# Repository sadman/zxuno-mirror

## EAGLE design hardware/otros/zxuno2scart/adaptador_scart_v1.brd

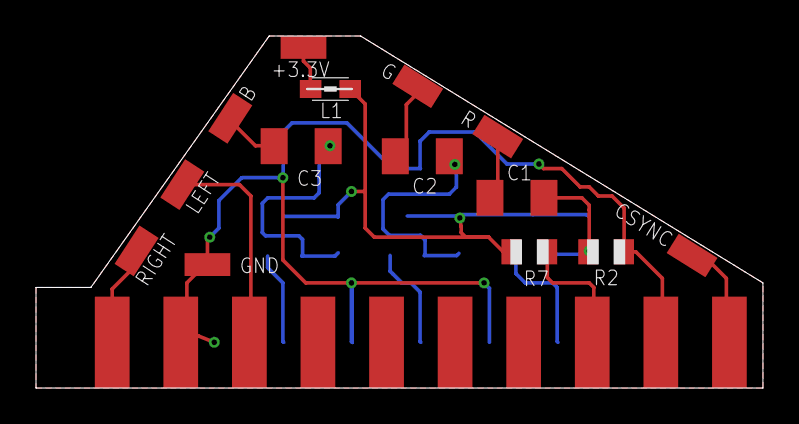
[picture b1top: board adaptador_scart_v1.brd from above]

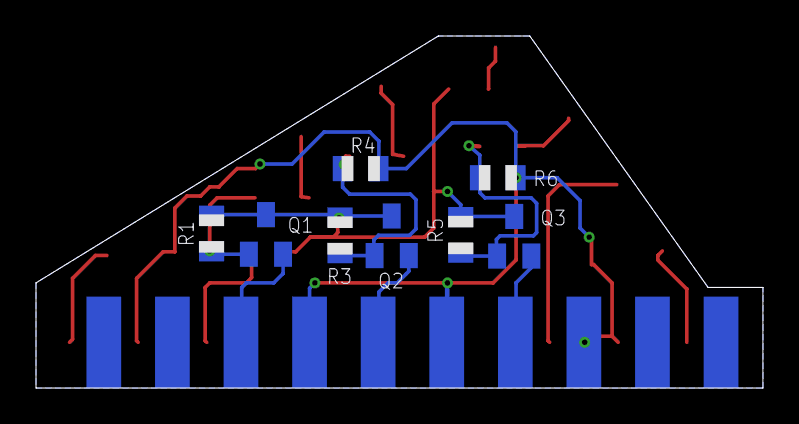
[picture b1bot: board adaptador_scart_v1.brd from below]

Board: 2 copper layers, 40.4 x 19.6 mm, 23 parts (9 on the bottom side), 16 nets.

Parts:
+3.3V: SMD1,27-2,54
B: SMD1,27-2,54
C1, C2, C3: 1uF; C1206K
CSYNC: SMD1,27-2,54
G: SMD1,27-2,54
GND: SMD1,27-2,54
L1: 0805
LEFT: SMD1,27-2,54
Q1, Q2, Q3: BC847C; SOT23
R: SMD1,27-2,54
R1, R3, R5: 10K; R0805
R2, R4, R6: 22K; R0805
R7: 50; R0805
RIGHT: SMD1,27-2,54
U$1: SCART-MALE-PCB; SCART-PCB

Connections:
BIN: B.1, C3.1
BOUT: Q3.2, U$1.7
CSYNC: CSYNC.1, U$1.20
FS: R7.1, U$1.16
GIN: C2.1, G.1
GND: GND.1, R2.1, R4.1, R6.1, U$1.4, U$1.5, U$1.9, U$1.13, U$1.18
GOUT: Q2.2, U$1.11
LEFT: LEFT.1, U$1.6
unnamed: C1.2, Q1.1, R1.1, R2.2
unnamed: C3.2, Q3.1, R5.1, R6.2
unnamed: C2.2, Q2.1, R3.1, R4.2
RIGHT: RIGHT.1, U$1.2
RIN: C1.1, R.1
ROUT: Q1.2, U$1.15
VCC: L1.2, Q1.3, Q2.3, Q3.3, R1.2, R3.2, R5.2, R7.2
VCCIN: +3.3V.1, L1.1

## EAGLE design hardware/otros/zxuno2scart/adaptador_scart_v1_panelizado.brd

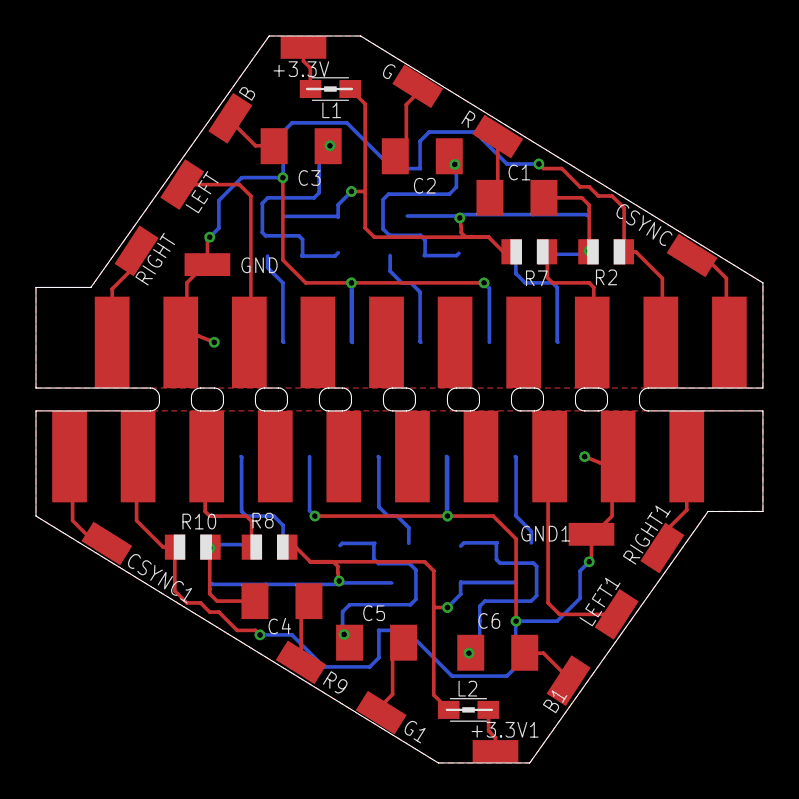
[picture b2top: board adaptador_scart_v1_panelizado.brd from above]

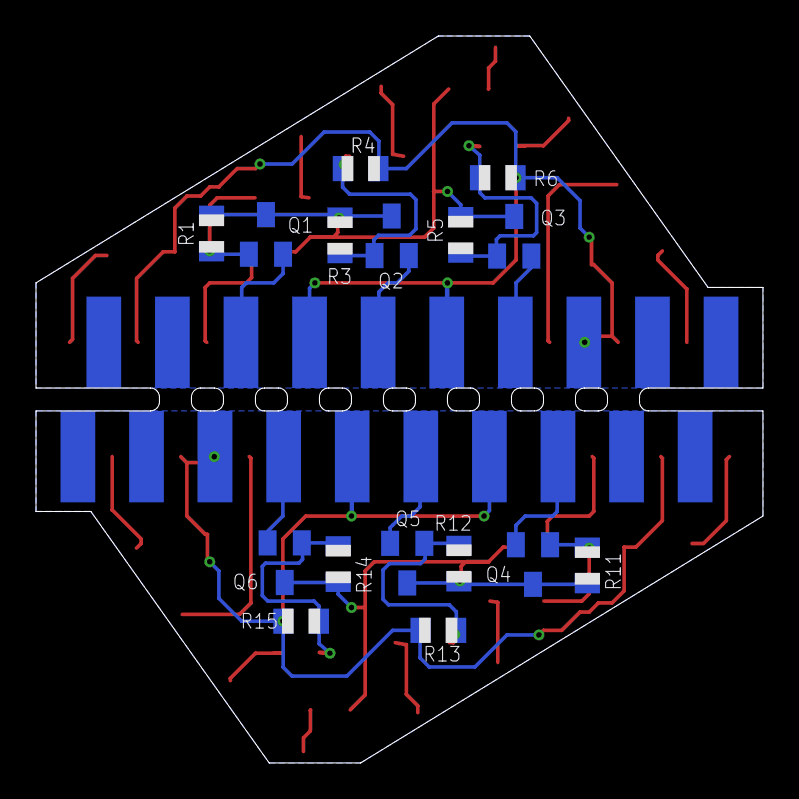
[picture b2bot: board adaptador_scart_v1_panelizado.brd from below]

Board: 2 copper layers, 40.4 x 40.4 mm, 46 parts (18 on the bottom side), 32 nets.

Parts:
+3.3V, +3.3V1: SMD1,27-2,54
B, B1: SMD1,27-2,54
C1, C2, C3, C4, C5, C6: 1uF; C1206K
CSYNC, CSYNC1: SMD1,27-2,54
G, G1: SMD1,27-2,54
GND, GND1: SMD1,27-2,54
L1, L2: 0805
LEFT, LEFT1: SMD1,27-2,54
Q1, Q2, Q3, Q4, Q5, Q6: BC847C; SOT23
R, R9: SMD1,27-2,54
R1, R3, R5, R11, R12, R14: 10K; R0805
R2, R4, R6, R10, R13, R15: 22K; R0805
R7, R8: 50; R0805
RIGHT, RIGHT1: SMD1,27-2,54
U$1, U$2: SCART-MALE-PCB; SCART-PCB

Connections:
BIN: B.1, C3.1
BIN1: B1.1, C6.1
BOUT: Q3.2, U$1.7
BOUT1: Q6.2, U$2.7
CSYNC: CSYNC.1, U$1.20
CSYNC1: CSYNC1.1, U$2.20
FS: R7.1, U$1.16
FS1: R8.1, U$2.16
GIN: C2.1, G.1
GIN1: C5.1, G1.1
GND: GND.1, R2.1, R4.1, R6.1, U$1.4, U$1.5, U$1.9, U$1.13, U$1.18
GND1: GND1.1, R10.1, R13.1, R15.1, U$2.4, U$2.5, U$2.9, U$2.13, U$2.18
GOUT: Q2.2, U$1.11
GOUT1: Q5.2, U$2.11
LEFT: LEFT.1, U$1.6
LEFT1: LEFT1.1, U$2.6
unnamed: C4.2, Q4.1, R10.2, R11.1
unnamed: C6.2, Q6.1, R14.1, R15.2
unnamed: C5.2, Q5.1, R12.1, R13.2
unnamed: C1.2, Q1.1, R1.1, R2.2
unnamed: C3.2, Q3.1, R5.1, R6.2
unnamed: C2.2, Q2.1, R3.1, R4.2
RIGHT: RIGHT.1, U$1.2
RIGHT1: RIGHT1.1, U$2.2
RIN: C1.1, R.1
RIN1: C4.1, R9.1
ROUT: Q1.2, U$1.15
ROUT1: Q4.2, U$2.15
VCC: L1.2, Q1.3, Q2.3, Q3.3, R1.2, R3.2, R5.2, R7.2
VCC1: L2.2, Q4.3, Q5.3, Q6.3, R8.2, R11.2, R12.2, R14.2
VCCIN: +3.3V.1, L1.1
VCCIN1: +3.3V1.1, L2.1

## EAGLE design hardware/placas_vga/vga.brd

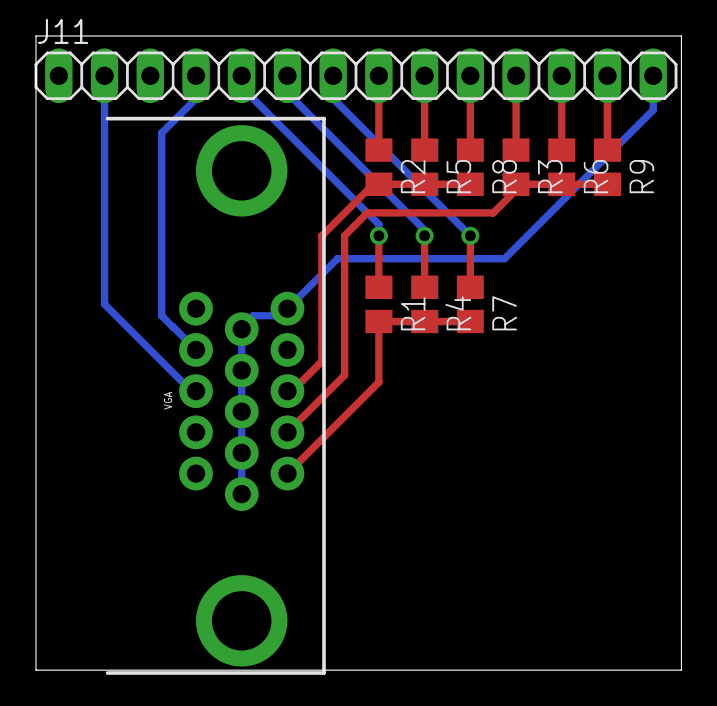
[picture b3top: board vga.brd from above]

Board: 2 copper layers, 35.9 x 35.2 mm, 11 parts (0 on the bottom side), 15 nets.

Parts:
J11: 1X14
R1, R2, R3: 470; R0805
R4, R5, R6: 1K; R0805
R7, R8, R9: 2K; R0805
VGA: DB15

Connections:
BLUE: R3.2, R6.2, R9.2, VGA.2
EXT1: J11.5, R1.1
EXT7: J11.6, R4.1
EXT13: J11.8, R2.1
EXT16: J11.9, R5.1
EXT19: J11.10, R8.1
EXT22: J11.11, R3.1
EXT25: J11.12, R6.1
EXT28: J11.13, R9.1
GREEN: R2.2, R5.2, R8.2, VGA.3
HSYNC: J11.2, VGA.13
unnamed: J11.14, VGA.5, VGA.6, VGA.7, VGA.8, VGA.9, VGA.10
unnamed: J11.7, R7.1
RED: R1.2, R4.2, R7.2, VGA.1
VSYNC: J11.4, VGA.14

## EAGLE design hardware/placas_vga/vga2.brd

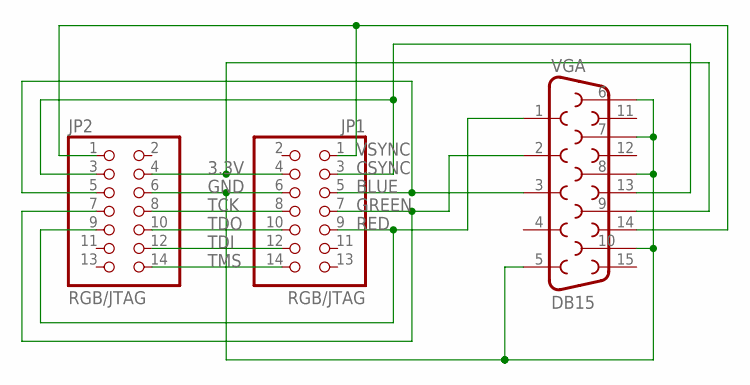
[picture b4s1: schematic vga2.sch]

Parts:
JP1, JP2: RGB/JTAG; 2X07
VGA: DB15

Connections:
3.3V: JP1.4, JP2.4, VGA.9
BLUE: JP1.5, JP2.5, VGA.3
CSYNC: JP1.3, JP2.3, VGA.13
GND: JP1.6, JP2.6, VGA.5, VGA.6, VGA.7, VGA.8, VGA.10
GREEN: JP1.7, JP2.7, VGA.2
RED: JP1.9, JP2.9, VGA.1
TCK: JP1.8, JP2.8
TDI: JP1.12, JP2.12
TDO: JP1.10, JP2.10
TMS: JP1.14, JP2.14
VSYNC: JP1.1, JP2.1, VGA.14

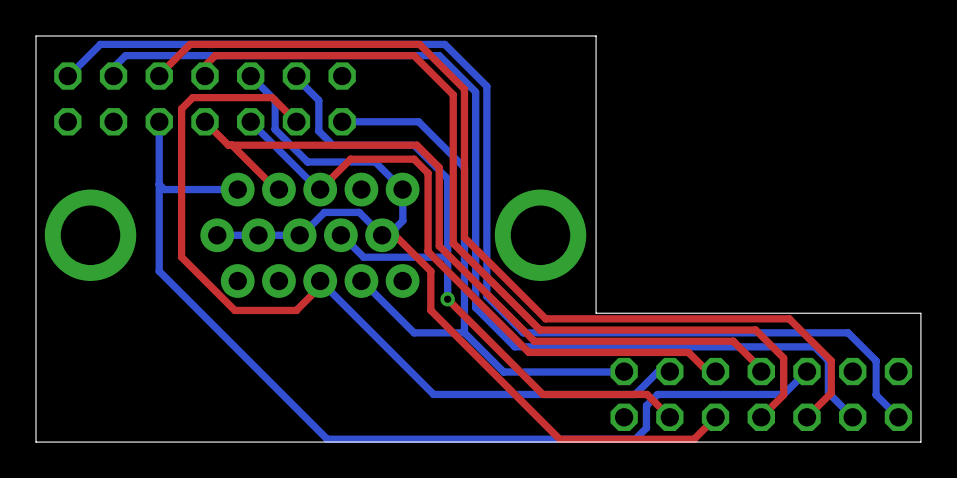
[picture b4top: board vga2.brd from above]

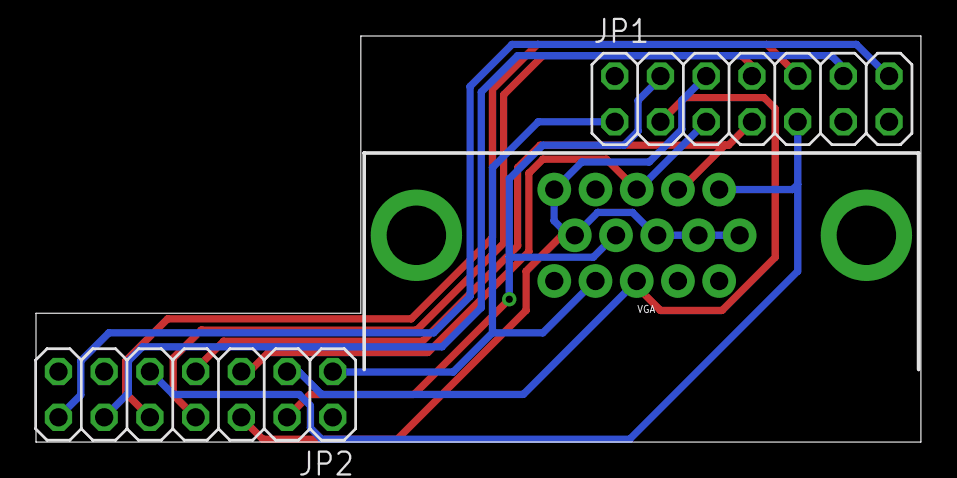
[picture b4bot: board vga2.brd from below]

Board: 2 copper layers, 49.2 x 22.6 mm, 3 parts (3 on the bottom side), 11 nets.

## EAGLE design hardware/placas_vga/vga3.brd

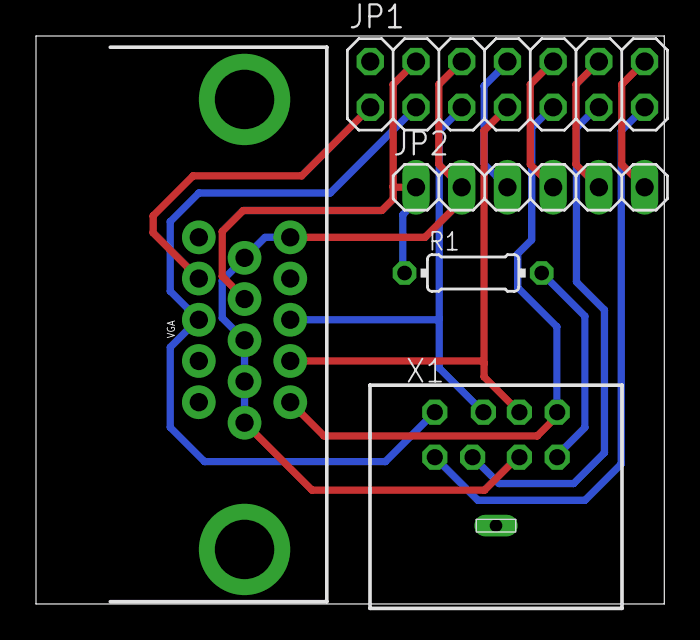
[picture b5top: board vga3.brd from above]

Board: 2 copper layers, 34.9 x 31.6 mm, 5 parts (0 on the bottom side), 14 nets.

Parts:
JP1: RGB/JTAG; 2X07
JP2: JTAG; 1X06
R1: 100; 0204/7
VGA: DB15
X1: MDIN08S

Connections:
3.3V: JP1.4, JP2.1, R1.1, VGA.9
BLUE: JP1.5, VGA.3, X1.7
CSYNC: JP1.3, VGA.13, X1.8
GND: JP1.6, JP2.2, VGA.5, VGA.6, VGA.7, VGA.8, VGA.10, X1.1
GREEN: JP1.7, VGA.2, X1.4
L-OUT: JP1.13, X1.5
unnamed: R1.2, X1.3
R-OUT: JP1.11, X1.2
RED: JP1.9, VGA.1, X1.6
TCK: JP1.8, JP2.3
TDI: JP1.12, JP2.5
TDO: JP1.10, JP2.4
TMS: JP1.14, JP2.6
VSYNC: JP1.1, VGA.14

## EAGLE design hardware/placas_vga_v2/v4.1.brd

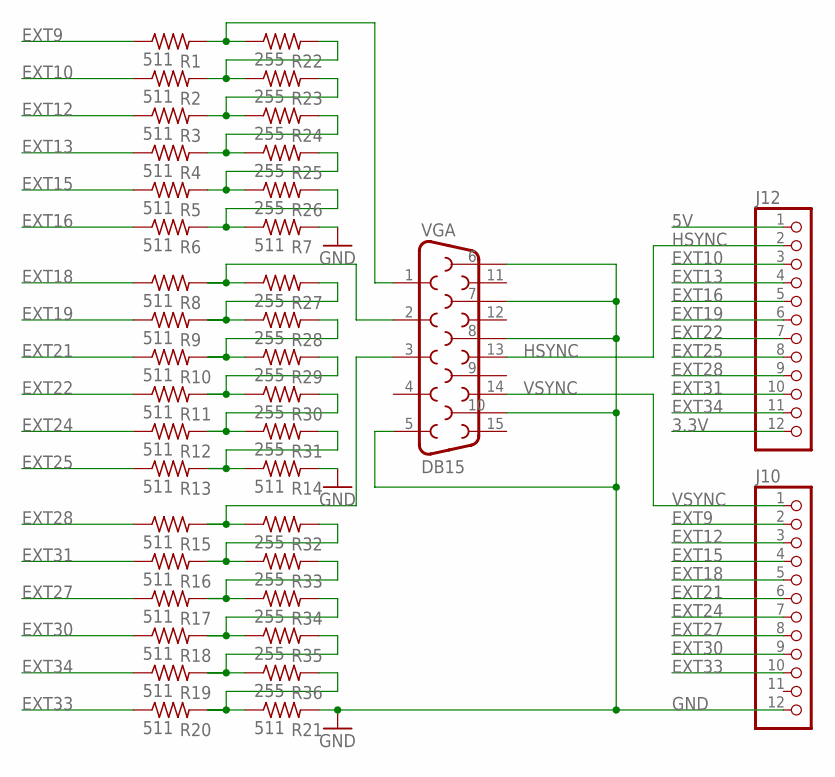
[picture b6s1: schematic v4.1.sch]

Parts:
J10, J12: PINHD-1X12; 1X12
R1, R2, R3, R4, R5, R6, R7, R8, R9, R10, R11, R12, R13, R14, R15, R16, R17, R18, R19, R20, R21: 511; R0805
R22, R23, R24, R25, R26, R27, R28, R29, R30, R31, R32, R33, R34, R35, R36: 255; R0805
VGA: DB15

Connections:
3.3V: J12.12
5V: J12.1
EXT9: J10.2, R1.1
EXT10: J12.3, R2.1
EXT12: J10.3, R3.1
EXT13: J12.4, R4.1
EXT15: J10.4, R5.1
EXT16: J12.5, R6.1
EXT18: J10.5, R8.1
EXT19: J12.6, R9.1
EXT21: J10.6, R10.1
EXT22: J12.7, R11.1
EXT24: J10.7, R12.1
EXT25: J12.8, R13.1
EXT27: J10.8, R17.1
EXT28: J12.9, R15.1
EXT30: J10.9, R18.1
EXT31: J12.10, R16.1
EXT33: J10.10, R20.1
EXT34: J12.11, R19.1
GND: J10.12, R7.2, R14.2, R21.2, VGA.5, VGA.6, VGA.7, VGA.8, VGA.10
GREEN: R8.2, R27.1, VGA.2
HSYNC: J12.2, VGA.13
unnamed: R20.2, R21.1, R36.2
unnamed: R9.2, R27.2, R28.1
unnamed: R2.2, R22.2, R23.1
unnamed: R1.2, R22.1, VGA.1
unnamed: R12.2, R30.2, R31.1
unnamed: R6.2, R7.1, R26.2
unnamed: R3.2, R23.2, R24.1
unnamed: R4.2, R24.2, R25.1
unnamed: R5.2, R25.2, R26.1
unnamed: R11.2, R29.2, R30.1
unnamed: R13.2, R14.1, R31.2
unnamed: R10.2, R28.2, R29.1
unnamed: R15.2, R32.1, VGA.3
unnamed: R16.2, R32.2, R33.1
unnamed: R17.2, R33.2, R34.1
unnamed: R18.2, R34.2, R35.1
unnamed: R19.2, R35.2, R36.1
VSYNC: J10.1, VGA.14

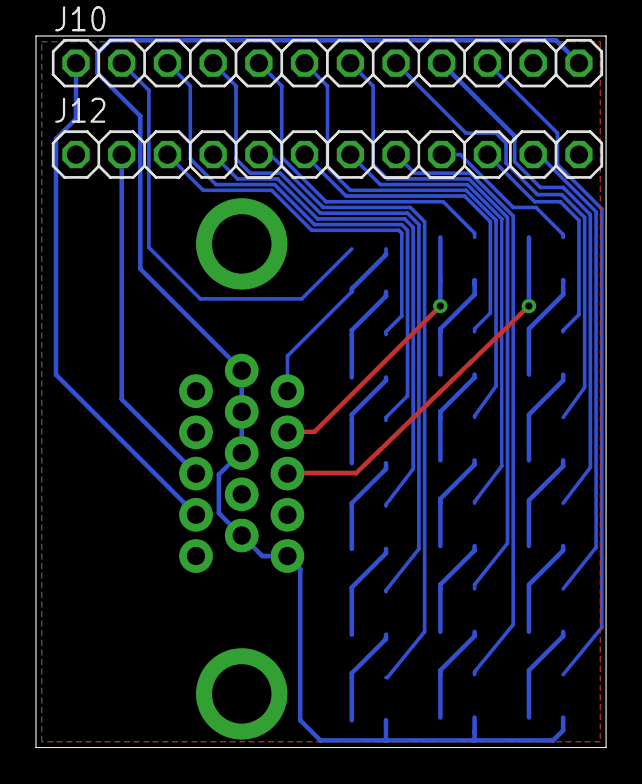
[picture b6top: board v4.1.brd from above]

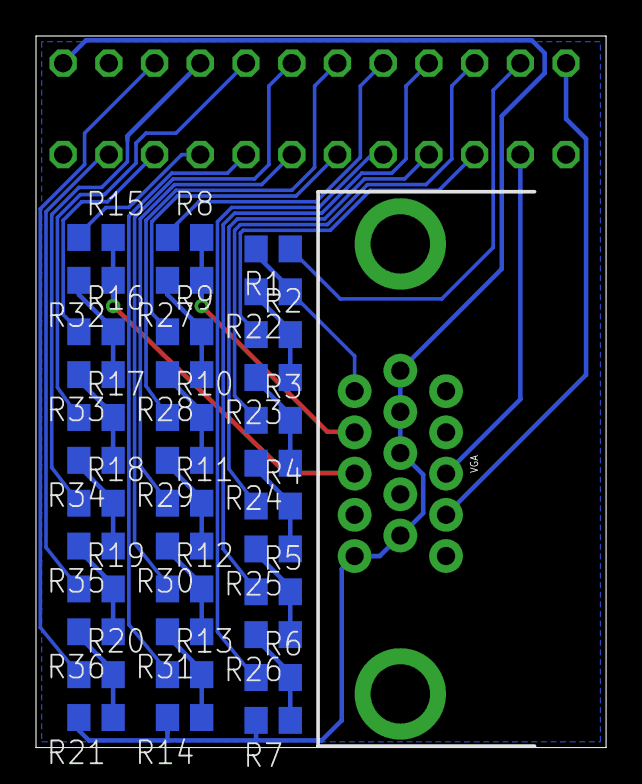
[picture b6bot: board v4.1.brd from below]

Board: 2 copper layers, 31.7 x 39.5 mm, 39 parts (37 on the bottom side), 39 nets.

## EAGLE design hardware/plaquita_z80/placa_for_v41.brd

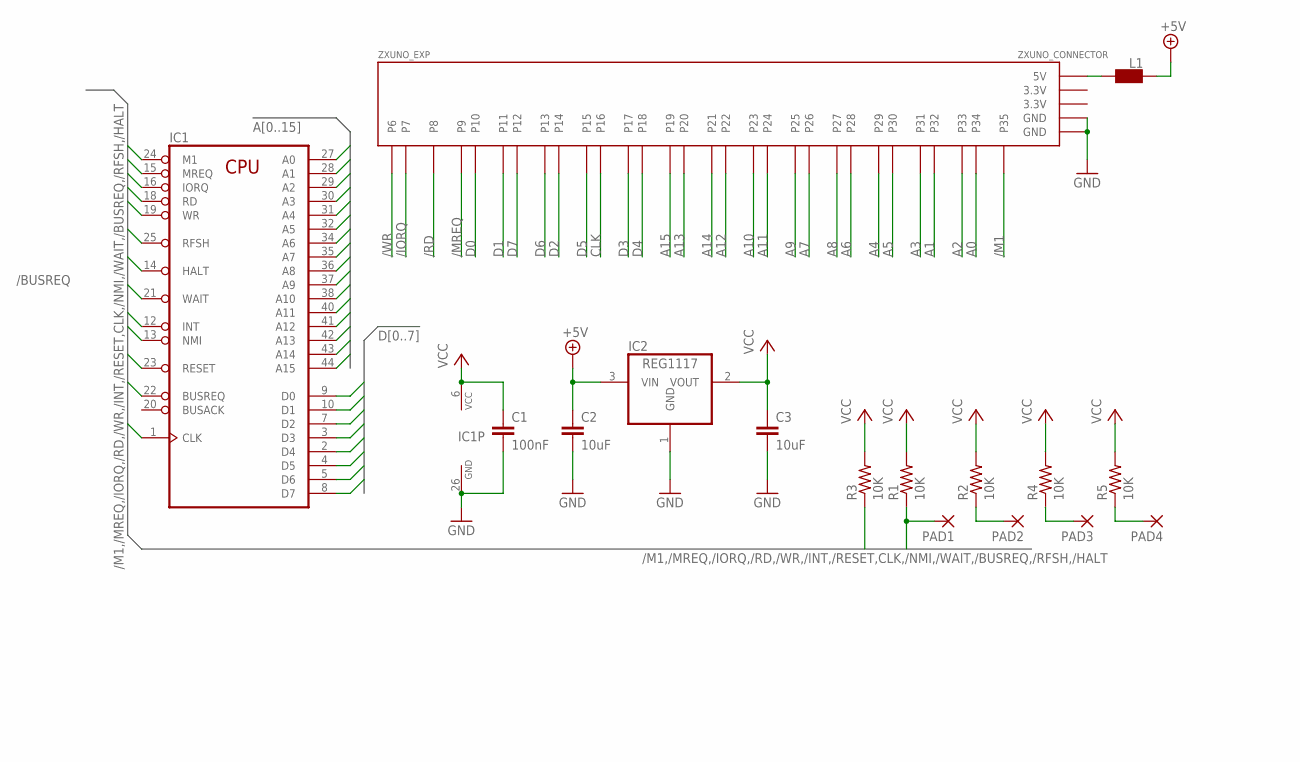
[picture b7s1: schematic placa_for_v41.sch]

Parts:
C1: 100nF; C0805K
C2, C3: 10uF; C0805K
IC1: Z80CPU-F; QFP-44
IC2: REG1117; SOT223
L1: WE-CBF_0805; 0805
PAD1, PAD2, PAD3, PAD4: SMD5; SMD2,54-5,08
R1, R2, R3, R4, R5: 10K; R0805
ZXUNO_EXP: ZXUNO_CONNECTOR

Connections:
3.3V: ZXUNO_EXP.3.3V@1 (3.3V), ZXUNO_EXP.3.3V@2 (3.3V)
+5V: C2.1, IC2.3 (VIN), L1.2
/BUSREQ: IC1.22 (BUSREQ), R3.1
/HALT: IC1.14 (HALT)
/INT: IC1.12 (INT)
/IORQ: IC1.16 (IORQ), ZXUNO_EXP.P7
/M1: IC1.24 (M1), ZXUNO_EXP.P35
/MREQ: IC1.15 (MREQ), ZXUNO_EXP.P9
/NMI: IC1.13 (NMI)
/RD: IC1.18 (RD), ZXUNO_EXP.P8
/RESET: IC1.23 (RESET)
/RFSH: IC1.25 (RFSH)
/WAIT: IC1.21 (WAIT), PAD1.1, R1.1
/WAIT1: PAD2.1, R2.1
/WAIT2: PAD3.1, R4.1
/WAIT3: PAD4.1, R5.1
/WR: IC1.19 (WR), ZXUNO_EXP.P6
A0: IC1.27 (A0), ZXUNO_EXP.P34
A1: IC1.28 (A1), ZXUNO_EXP.P32
A2: IC1.29 (A2), ZXUNO_EXP.P33
A3: IC1.30 (A3), ZXUNO_EXP.P31
A4: IC1.31 (A4), ZXUNO_EXP.P29
A5: IC1.32 (A5), ZXUNO_EXP.P30
A6: IC1.34 (A6), ZXUNO_EXP.P28
A7: IC1.35 (A7), ZXUNO_EXP.P26
A8: IC1.36 (A8), ZXUNO_EXP.P27
A9: IC1.37 (A9), ZXUNO_EXP.P25
A10: IC1.38 (A10), ZXUNO_EXP.P23
A11: IC1.40 (A11), ZXUNO_EXP.P24
A12: IC1.41 (A12), ZXUNO_EXP.P22
A13: IC1.42 (A13), ZXUNO_EXP.P20
A14: IC1.43 (A14), ZXUNO_EXP.P21
A15: IC1.44 (A15), ZXUNO_EXP.P19
CLK: IC1.1 (CLK), ZXUNO_EXP.P16
D0: IC1.9 (D0), ZXUNO_EXP.P10
D1: IC1.10 (D1), ZXUNO_EXP.P11
D2: IC1.7 (D2), ZXUNO_EXP.P14
D3: IC1.3 (D3), ZXUNO_EXP.P17
D4: IC1.2 (D4), ZXUNO_EXP.P18
D5: IC1.4 (D5), ZXUNO_EXP.P15
D6: IC1.5 (D6), ZXUNO_EXP.P13
D7: IC1.8 (D7), ZXUNO_EXP.P12
GND: C1.2, C2.2, C3.2, IC1.26 (GND), IC2.1 (GND), ZXUNO_EXP.GND@1 (GND), ZXUNO_EXP.GND@2 (GND)
unnamed: L1.1, ZXUNO_EXP.5V
VCC: C1.1, C3.1, IC1.6 (VCC), IC2.2 (VOUT), R1.2, R2.2, R3.2, R4.2, R5.2

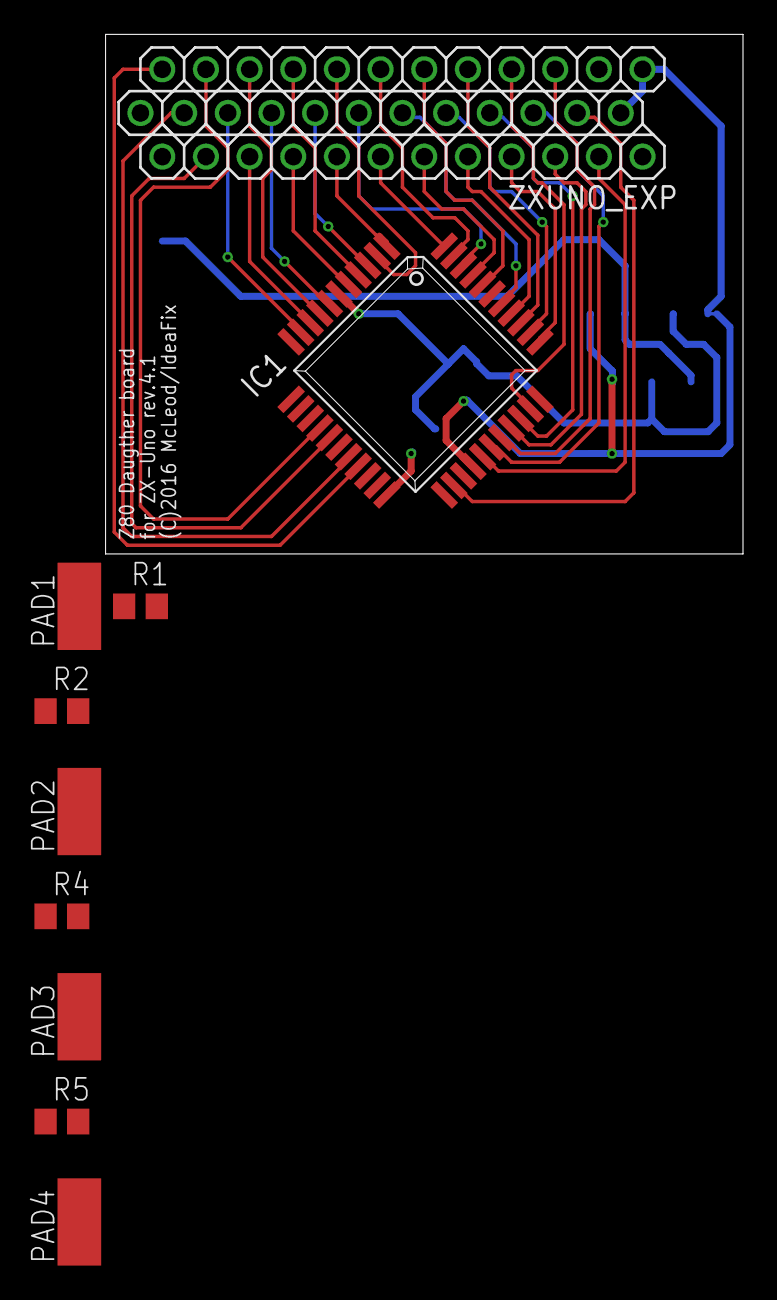
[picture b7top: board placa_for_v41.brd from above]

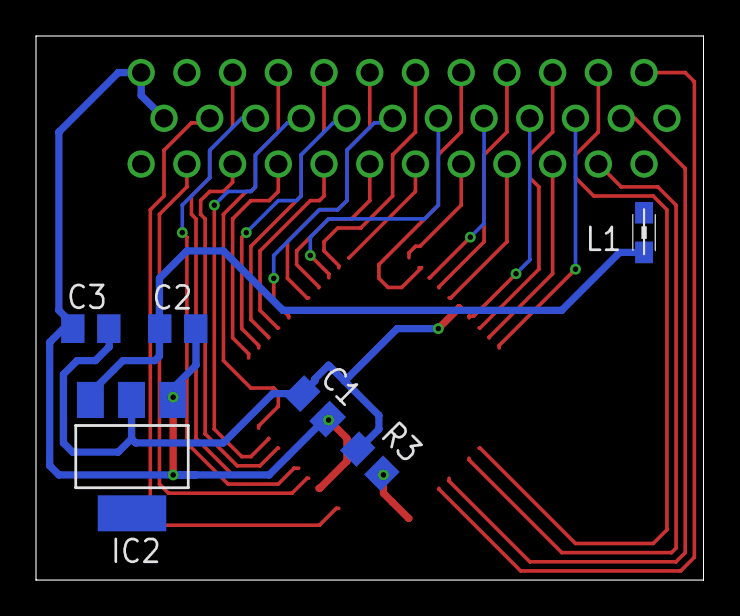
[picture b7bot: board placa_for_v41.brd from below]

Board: 2 copper layers, 37.1 x 30.2 mm, 16 parts (6 on the bottom side), 40 nets.

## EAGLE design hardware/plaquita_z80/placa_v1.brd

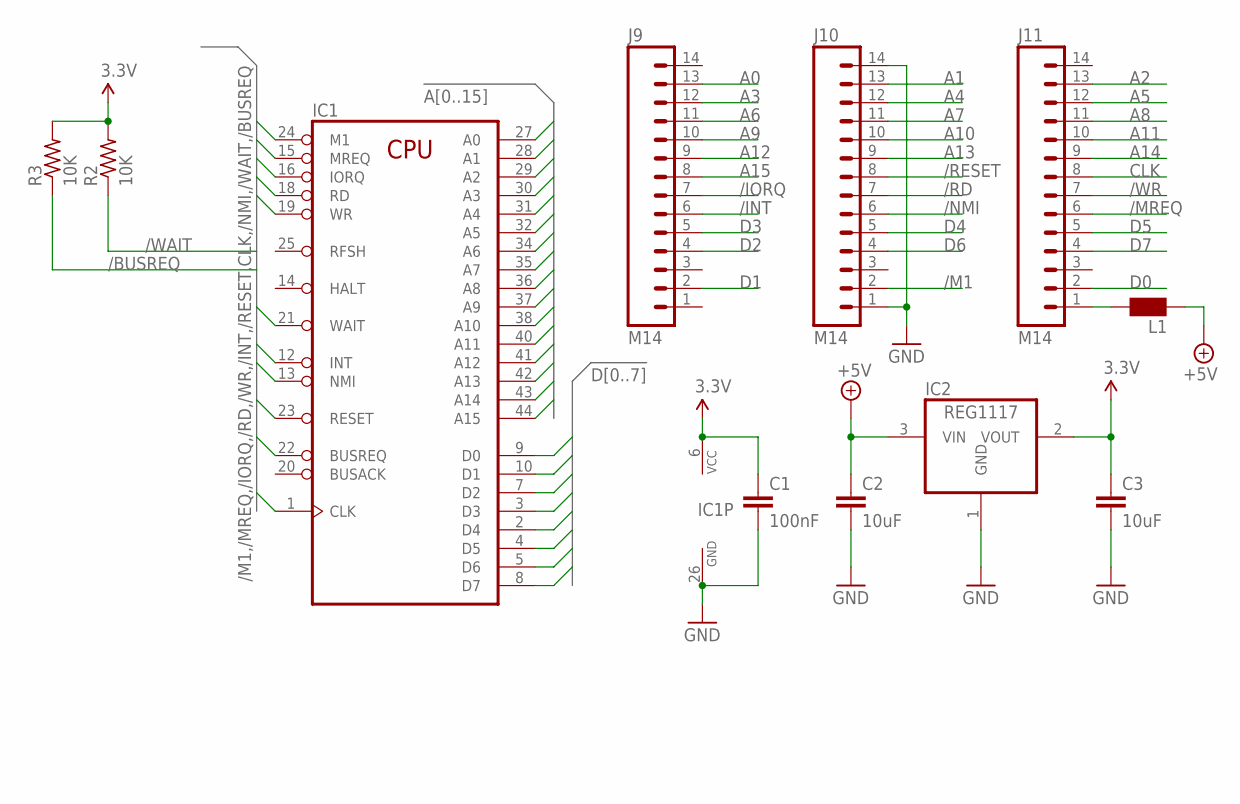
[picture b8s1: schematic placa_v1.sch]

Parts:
C1: 100nF; C0805K
C2, C3: 10uF; C0805K
IC1: Z80CPU-F; QFP-44
IC2: REG1117; SOT223
J9, J10, J11: M14; 1X14
L1: WE-CBF_0805; 0805
R2, R3: 10K; R0805

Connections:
3.3V: C1.1, C3.1, IC1.6 (VCC), IC2.2 (VOUT), R2.2, R3.2
+5V: C2.1, IC2.3 (VIN), L1.2
/BUSREQ: IC1.22 (BUSREQ), R3.1
/INT: IC1.12 (INT), J9.6
/IORQ: IC1.16 (IORQ), J9.7
/M1: IC1.24 (M1), J10.2
/MREQ: IC1.15 (MREQ), J11.6
/NMI: IC1.13 (NMI), J10.6
/RD: IC1.18 (RD), J10.7
/RESET: IC1.23 (RESET), J10.8
/WAIT: IC1.21 (WAIT), R2.1
/WR: IC1.19 (WR), J11.7
A0: IC1.27 (A0), J9.13
A1: IC1.28 (A1), J10.13
A2: IC1.29 (A2), J11.13
A3: IC1.30 (A3), J9.12
A4: IC1.31 (A4), J10.12
A5: IC1.32 (A5), J11.12
A6: IC1.34 (A6), J9.11
A7: IC1.35 (A7), J10.11
A8: IC1.36 (A8), J11.11
A9: IC1.37 (A9), J9.10
A10: IC1.38 (A10), J10.10
A11: IC1.40 (A11), J11.10
A12: IC1.41 (A12), J9.9
A13: IC1.42 (A13), J10.9
A14: IC1.43 (A14), J11.9
A15: IC1.44 (A15), J9.8
CLK: IC1.1 (CLK), J11.8
D0: IC1.9 (D0), J11.2
D1: IC1.10 (D1), J9.2
D2: IC1.7 (D2), J9.4
D3: IC1.3 (D3), J9.5
D4: IC1.2 (D4), J10.5
D5: IC1.4 (D5), J11.5
D6: IC1.5 (D6), J10.4
D7: IC1.8 (D7), J11.4
GND: C1.2, C2.2, C3.2, IC1.26 (GND), IC2.1 (GND), J10.1, J10.14
unnamed: J11.1, L1.1

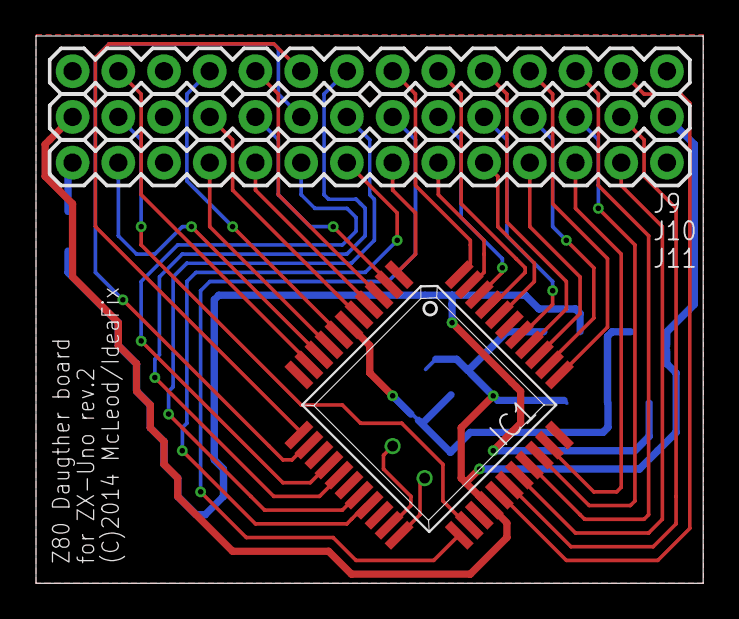
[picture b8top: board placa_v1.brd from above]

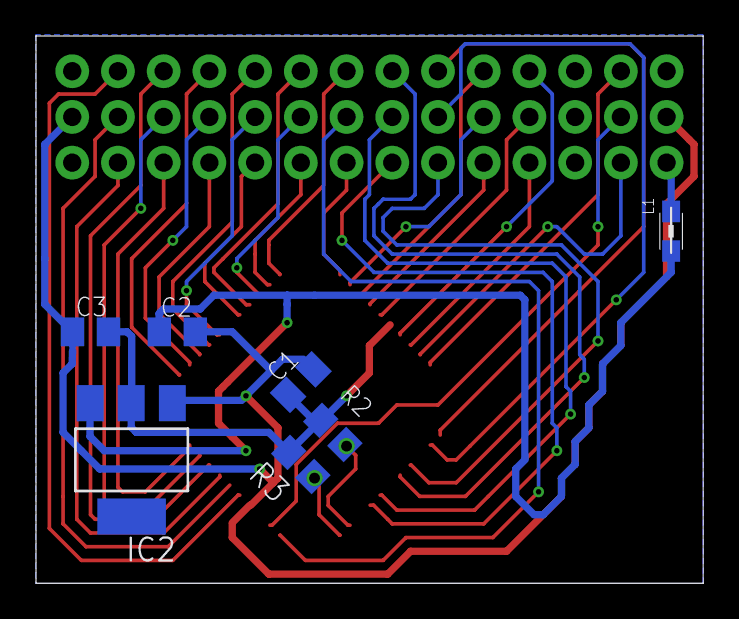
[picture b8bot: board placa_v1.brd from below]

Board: 2 copper layers, 37.1 x 30.4 mm, 11 parts (7 on the bottom side), 39 nets.

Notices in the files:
hardware/plaquita_z80/placa_for_v41.brd:
(C)2016 McLeod/IdeaFix
hardware/plaquita_z80/placa_v1.brd:
(C)2014 McLeod/IdeaFix
parts and their libraries:
wuerth-elektronik: Copyright: Würth Elektronik eiSos
SparkFun-Connectors: Licensing: Creative Commons ShareAlike 4.0 International - https://creativecommons.org/licenses/by-sa/4.0
SparkFun-Connectors: Licensing: CC v3.0 Share-Alike You are welcome to use this library for commercial purposes.
